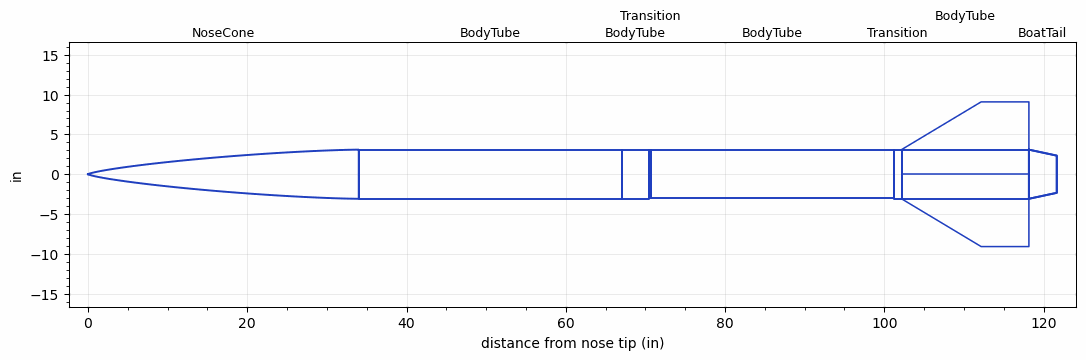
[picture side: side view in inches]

<RASAeroDocument>
 <FileVersion>2</FileVersion>
 <RocketDesign>
  <NoseCone>
   <Length>33.9999</Length>
   <Diameter>6.17</Diameter>
   <Shape>Von Karman Ogive</Shape>
   <Location>0</Location>
  </NoseCone>
  <BodyTube>
   <Length>32.9999</Length>
   <Diameter>6.17</Diameter>
   <Location>33.9999</Location>
  </BodyTube>
  <BodyTube>
   <Length>3.5</Length>
   <Diameter>6.17</Diameter>
   <RailGuideDiameter>0.4375</RailGuideDiameter>
   <RailGuideHeight>0.2975</RailGuideHeight>
   <Location>66.9998</Location>
  </BodyTube>
  <Transition>
   <Length>0.25</Length>
   <Diameter>6</Diameter>
   <Location>70.4998</Location>
   <RearDiameter>6</RearDiameter>
  </Transition>
  <BodyTube>
   <Length>30.4099</Length>
   <Diameter>6</Diameter>
   <Location>70.7498</Location>
  </BodyTube>
  <Transition>
   <Length>1</Length>
   <Diameter>6.17</Diameter>
   <Location>101.1597</Location>
   <RearDiameter>6.17</RearDiameter>
  </Transition>
  <BodyTube>
   <Length>16</Length>
   <Diameter>6.17</Diameter>
   <Location>102.1597</Location>
   <BoattailLength>3.5</BoattailLength>
   <BoattailRearDiameter>4.67</BoattailRearDiameter>
   <Fin>
    <Count>4</Count>
    <Chord>16</Chord>
    <Span>6</Span>
    <SweepDistance>10</SweepDistance>
    <TipChord>6</TipChord>
    <Thickness>0.52</Thickness>
    <Location>16</Location>
    <AirfoilSection>Square</AirfoilSection>
   </Fin>
  </BodyTube>
  <BoatTail>
   <Length>3.5</Length>
   <Diameter>6.17</Diameter>
   <RearDiameter>4.67</RearDiameter>
   <Location>118.1597</Location>
  </BoatTail>
  <Surface>Rough Camouflage Paint</Surface>
  <ModifiedBarrowman>False</ModifiedBarrowman>
  <Turbulence>False</Turbulence>
  <UseBooster1>False</UseBooster1>
  <UseBooster2>False</UseBooster2>
 </RocketDesign>
 <LaunchSite>
  <Altitude>0</Altitude>
  <Pressure>29.9214</Pressure>
  <RodAngle>0</RodAngle>
  <RodLength>3.2808</RodLength>
  <Temperature>59</Temperature>
  <WindSpeed>4.4739</WindSpeed>
 </LaunchSite>
 <Recovery>
  <Altitude1>0</Altitude1>
  <Altitude2>0</Altitude2>
  <DeviceType1>None</DeviceType1>
  <DeviceType2>None</DeviceType2>
  <Event1>False</Event1>
  <Event2>False</Event2>
  <Size1>0</Size1>
  <Size2>0</Size2>
  <EventType1>None</EventType1>
  <EventType2>None</EventType2>
  <CD1>0</CD1>
  <CD2>0</CD2>
 </Recovery>
 <SimulationList>
  <Simulation>
   <SustainerEngine>N8406  (MITRT)</SustainerEngine>
   <SustainerLaunchWt>92.06</SustainerLaunchWt>
   <SustainerCG>79.98</SustainerCG>
   <SustainerIgnitionDelay>0</SustainerIgnitionDelay>
   <Booster1SeparationDelay>0</Booster1SeparationDelay>
   <Booster1IgnitionDelay>0</Booster1IgnitionDelay>
   <IncludeBooster1>False</IncludeBooster1>
   <Booster2Delay>0</Booster2Delay>
   <IncludeBooster2>False</IncludeBooster2>
   <TimetoApogee>24.23046</TimetoApogee>
   <MaxAltitude>11619.93</MaxAltitude>
   <MaxVelocity>1332.337</MaxVelocity>
  </Simulation>
 </SimulationList>
</RASAeroDocument>
